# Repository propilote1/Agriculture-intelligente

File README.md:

# Agriculture-intelligente
Système intelligent d’analyse et de diagnostic des sols basé sur la mesure du NPK, du pH, de l’humidité du sol et de l’air, de la température et du rayonnement solaire (pyranomètre), afin d’évaluer la fertilité du sol et de déterminer les cultures les mieux adaptées.

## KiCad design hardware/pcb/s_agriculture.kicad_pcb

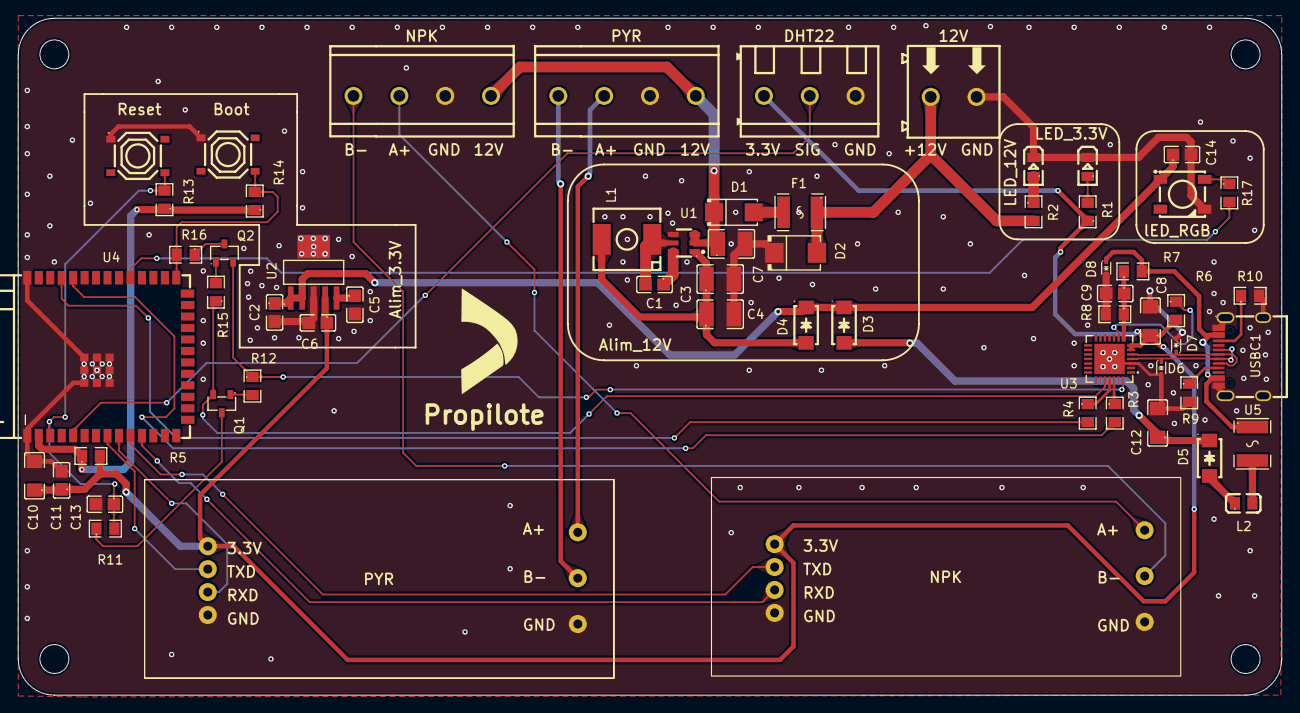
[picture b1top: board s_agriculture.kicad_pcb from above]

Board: 2 copper layers, 140.0 x 75.0 mm, 65 parts (0 on the bottom side), 46 nets.

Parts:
Boot: TS-1187A-B-A-B; C318884_SW-SMD_4P-L5_1-W5_1-P3_70-LS6_5-TL_H1_5
C1: 100nF(104) ±10% 50V; C49678_C0805
C2, C6: 1uF; C28323_C0805
C3, C4: CC1210KKX7R8BB226; C5341638_C1210
C5: 10nF; C83170_C0805
C7: CC1210X7R50V106MN; C53084458_C1210
C8, C10, C12: 10uF; C14860_C1206
C9: 1uF; C94122_C0805
C11, C14: 0.1uF; C49678_C0805
C13: 1uF/16V; C94122_C0805
D1: SS34; C8678_SMA_L4_3-W2_6-LS5_2-RD
D2: SMBJ15A_C188412; C188412_SMB_L4_6-W3_6-LS5_3-RD
D3, D4, D5: SS14; C2480_SMA_L4_2-W2_6-LS5_0-RD_1
D6, D7, D8: LESD5D5; C5199850_SOD-523_L1_2-W0_8-LS1_6-BI
F1: BSMD1812-200-30V; C960026_F1812
H1, H2, H3, H4: MountingHole; MountingHole_3.2mm_M3
L1: SPM6530T-4R7M; C76857_IND-SMD_L7_1-W6_5
L2: EMI(600Ω); C21519_L0805
LED1: Verte; C84260_LED0805-R-RD
LED2: Rouge; C84260_LED0805-R-RD
P1: Alim 12V; C8465_CONN-TH_2P-P5_00_WJ500V-5_08-2P
P2: DHT22; C72334_CONN-TH_3P-P5_00_WJ500V-5_08-3P
Q1, Q2: L8050QLT1G; C49581_SOT-23-3_L2_9-W1_3-P1_90-LS2_4-BR
R1: 220Ω; C17557_R0805
R2: 2.2KΩ (2201) ±1%; C17520_R0805
R3, R4, R5, R11, R16: 0Ω; C17477_R0805
R6: 1KΩ; C17513_R0805
R7: 22.1KΩ; C17552_R0805
R8: 47.5KΩ; C26011_R0805
R9, R10: 5.1KΩ; C27834_R0805
R12, R13, R14, R15: 10KΩ; C17414_R0805
R17: 330Ω; C17630_R0805
Reset: TS-1187A-B-A-B; C318884_SW-SMD_4P-L5_1-W5_1-P3_70-LS6_5-TL_H1_5
U1: AP63205WU-7; C2071056_TSOT-23-6_L2_9-W1_6-P0_95-LS2_8-BL
U2: TPS79533DCQR; C28669_SOT-223-6_L6_5-W3_5-P1_27-BR
U3: CP2102N-A02-GQFN28R; C964632_QFN-28_L5_0-W5_0-P0_50-TL-EP3_3
U4: ESP32-S3-WROOM-1(N8R2); C2913204_WIRELM-SMD_ESP32-S3-WROOM-1
U5: polyfusible; C17313_F1812
U6, U7: RS485-TTL
U8: NPK(7-1); C42377749_CONN-TH_WJ500V-5_08-4P
U9: PYR; C42377749_CONN-TH_WJ500V-5_08-4P
USBC1: TYPE-C-31-M-12; C165948_USB-C_SMD-TYPE-C-31-M-12_1
lED_RGB: WS2812B-B/W; C2761795_LED-SMD_4P-L5_0-W5_0-TL_WS2812B-B

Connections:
+3.3V: C6.1, C8.1, C10.1, C11.1, P2.3, R1.1, R5.2, R6.2, U2.4 (OUT), U3.6 (VDD), U3.7 (VREGIN), U6.1 (VCC), U7.1 (VCC)
+5V: C2.1, C14.1, D3.1 (K), D4.1 (K), U2.1 (EN), U2.2 (IN), lED_RGB.1 (VDD)
+12V: D2.2 (A), F1.1, P1.1, R2.2
+12V_P: C7.1, D1.1 (K), U1.2 (EN), U1.3 (VIN), U8.1, U9.1
DTR: Q2.2 (E), R12.1, U3.28 (DTR)
EN: C13.1, R11.2, R13.2, Reset.4 (D), U4.3 (EN)
ESP_3.3V: R5.1, R13.1, R14.1, U4.2 (3V3)
GND: Boot.1 (A), C2.2, C3.2, C4.2, C5.2, C6.2, C7.2, C8.2, C9.2, C10.2, C11.2, C12.2, C13.2, C14.2, D2.1 (K), D6.2, D7.2, D8.2, LED1.2 (K), LED2.2 (K), P1.2, P2.1, R8.2, R9.2, R10.2, Reset.1 (A), U1.4 (GND), U2.3 (GND), U2.6 (GND), U3.3 (GND), U3.29 (EP), U4.1 (GND), U4.40 (GND), U4.41 (GND), U6.4 (GND), U6.7 (Ground), U7.4 (GND), U7.7 (Ground), U8.2, U9.2, USBC1.1 (EH), USBC1.2 (EH), USBC1.3 (EH), USBC1.4 (EH), USBC1.A1B12 (GND), USBC1.B1A12 (GND), lED_RGB.3 (VSS)
GPIO0: Boot.4 (D), R14.2, R16.2, U4.27 (IO0)
GPIO5: P2.2, U4.5 (IO5)
GPIO15: U4.8 (IO15), U6.2 (TXD)
GPIO16: U4.9 (IO16), U6.3 (RXD)
GPIO17: U4.10 (IO17), U7.2 (TXD)
GPIO18: U4.11 (IO18), U7.3 (RXD)
GPIO38: R17.2, U4.31 (IO38)
unnamed: D1.2 (A), F1.2
unnamed: D5.2 (A), L2.1
unnamed: L2.2, U5.2
unnamed: LED1.1 (A), R1.2
unnamed: LED2.1 (A), R2.1
unnamed: R17.1, lED_RGB.4 (DIN)
unnamed: Q1.1 (B), R12.2
unnamed: Q1.3 (C), R11.1
unnamed: Q2.1 (B), R15.2
unnamed: Q2.3 (C), R16.1
unnamed: C1.1, U1.6 (BST)
unnamed: C1.2, L1.1, U1.5 (SW)
unnamed: C5.1, U2.5 (NR)
unnamed: R6.1, U3.9 (RSTb)
unnamed: R4.1, U3.25 (RXD)
unnamed: R3.1, U3.26 (TXD)
unnamed: C9.1, R7.1, R8.1, U3.8 (VBUS)
unnamed: U6.5 (A+), U9.3
unnamed: U6.6 (B-), U9.4
unnamed: U7.5 (A+), U8.3
unnamed: U7.6 (B-), U8.4
unnamed: R9.1, USBC1.A5 (CC1)
unnamed: R10.1, USBC1.B5 (CC2)
RTS: Q1.2 (E), R15.1, U3.24 (RTS)
U0RXD: R3.2, U4.36 (RXD0)
U0TXD: R4.2, U4.37 (TXD0)
USB_DN: D7.1, U3.5 (D-), USBC1.A7 (DN1), USBC1.B7 (DN2)
USB_DP: D6.1, U3.4 (D+), USBC1.A6 (DP1), USBC1.B6 (DP2)
VBUS: D8.1, R7.2, U5.1, USBC1.A4B9 (VBUS), USBC1.B4A9 (VBUS)
buk_5V: C3.1, C4.1, D4.2 (A), L1.2, U1.1 (FB)
usb_5V: C12.1, D3.2 (A), D5.1 (K)
